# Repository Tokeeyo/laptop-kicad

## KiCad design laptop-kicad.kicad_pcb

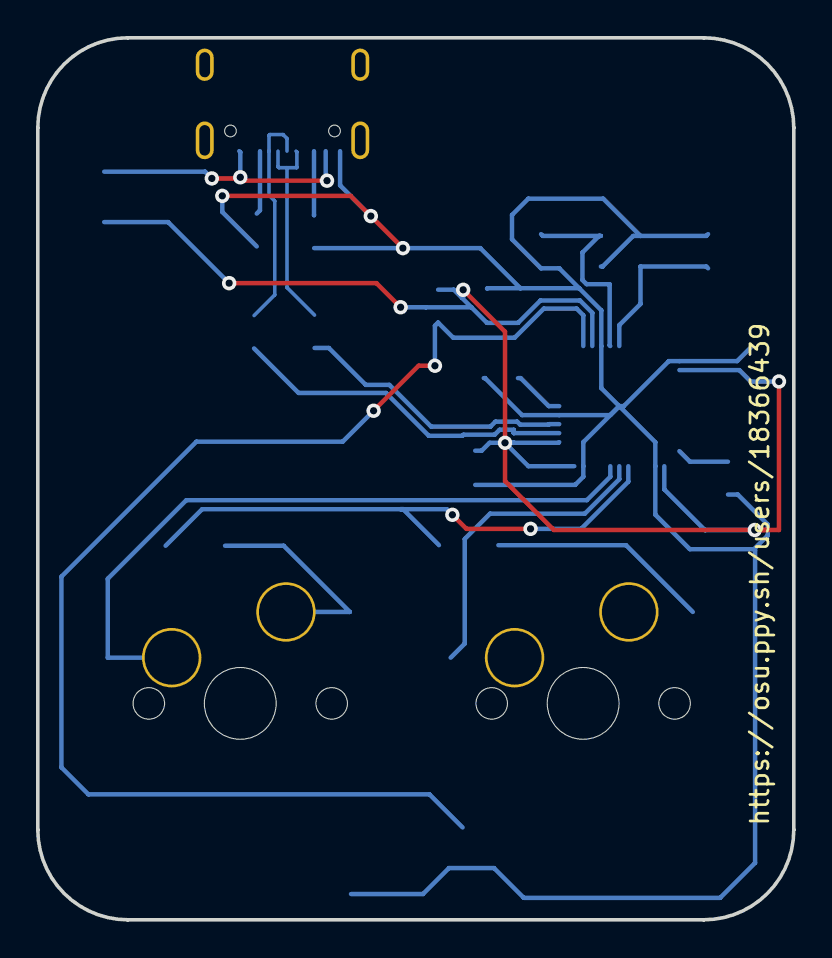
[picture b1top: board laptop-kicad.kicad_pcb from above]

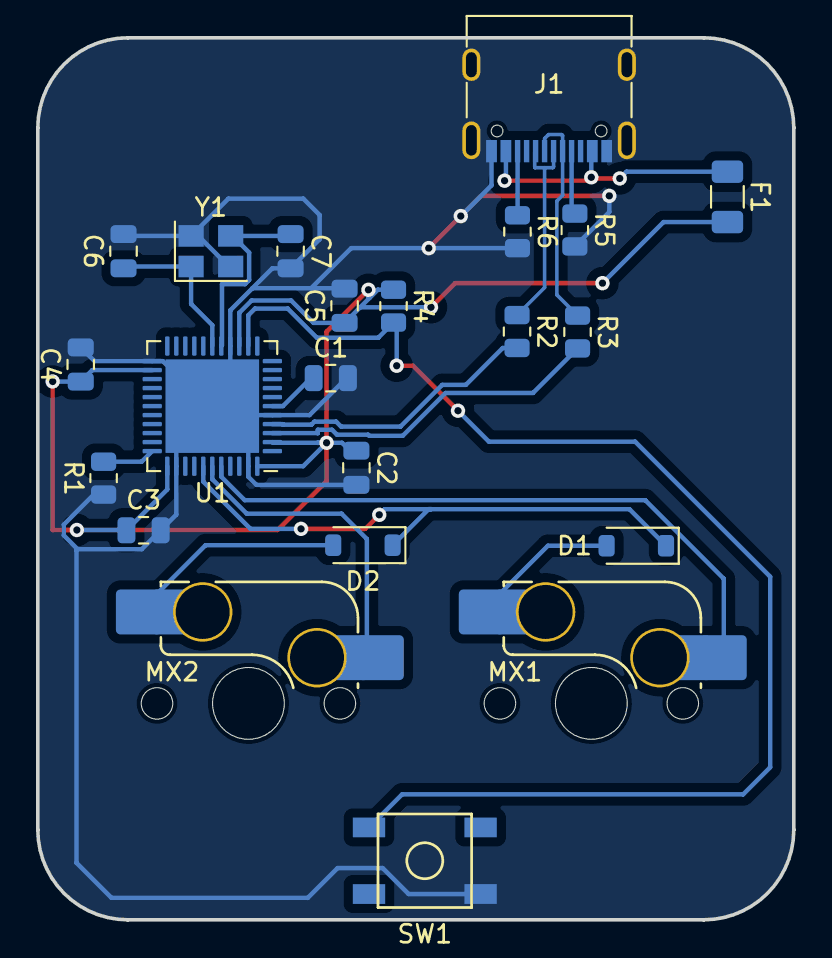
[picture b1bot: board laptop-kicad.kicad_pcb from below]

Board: 2 copper layers, 42.0 x 49.0 mm, 22 parts (22 on the bottom side), 19 nets.

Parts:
C1: 1uF; C_0805_2012Metric
C2, C3, C4: 0.1uF; C_0805_2012Metric
C5: 10uF; C_0805_2012Metric
C6, C7: 22pF; C_0805_2012Metric
D1, D2: D_Small; D_SOD-123
F1: 500mA; Fuse_1206_3216Metric
J1: USB_C_Receptacle_USB2.0; USB_C_Receptacle_G-Switch_GT-USB-7010ASV
MX1, MX2: MX_SW_HS; SW_MX_HS_1u
R1, R4: 10k; R_0805_2012Metric
R2, R3: 22; R_0805_2012Metric
R5, R6: 5.1k; R_0805_2012Metric
SW1: SW_Push; SKQG-1155865
U1: ATmega32U4-M; QFN-44-1EP_7x7mm_P0.5mm_EP5.2x5.2mm
Y1: 16MHz; Crystal_SMD_3225-4Pin_3.2x2.5mm

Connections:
+5V: C2.1, C3.1, C4.1, C5.1, F1.2, R4.1, U1.2 (UVCC), U1.7 (VBUS), U1.14 (VCC), U1.24 (AVCC), U1.34 (VCC), U1.44 (AVCC)
COL0: MX1.1, U1.40 (PF1)
COL1: MX2.1, U1.39 (PF4)
DBUS+: J1.A6 (D+), J1.B6 (D+), R2.1
DBUS-: J1.A7 (D-), J1.B7 (D-), R3.1
GND: C1.2, C2.2, C3.2, C4.2, C5.2, C6.2, C7.1, J1.A1 (GND), J1.A12 (GND), J1.B1 (GND), J1.B12 (GND), J1.S1 (SHIELD), R1.1, R5.2, R6.2, SW1.1, U1.5 (UGND), U1.15 (GND), U1.23 (GND), U1.35 (GND), U1.43 (GND), U1.45 (GND), Y1.2, Y1.4
unnamed: D1.2 (A), MX1.2
unnamed: D2.2 (A), MX2.2
unnamed: J1.A5 (CC1), R5.1
unnamed: J1.B5 (CC2), R6.1
unnamed: R2.2, U1.4 (D+)
unnamed: R3.2, U1.3 (D-)
unnamed: C1.1, U1.6 (UCAP)
unnamed: C6.2, U1.17 (XTAL1), Y1.1
unnamed: C7.2, U1.16 (XTAL2), Y1.3
unnamed: R1.2, U1.33 (~HWB/PE2)
unnamed: R4.2, SW1.2, U1.13 (~RESET)
ROW0: D1.1 (K), D2.1 (K), U1.38 (PF5)
VBUS: F1.1, J1.A4 (VBUS), J1.A9 (VBUS), J1.B4 (VBUS), J1.B9 (VBUS)

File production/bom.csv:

Designator,Footprint,Quantity,Value,LCSC Part #
C1,0805,1,1uF,
"C2, C3, C4",0805,3,0.1uF,
C5,0805,1,10uF,
"C6, C7",0805,2,22pF,
"D1, D2",D_SOD-123,2,D_Small,
F1,1206,1,500mA,
J1,USB_C_Receptacle_G-Switch_GT-USB-7010ASV,1,USB_C_Receptacle_USB2.0,
"MX1, MX2",SW_MX_HS_1u,2,MX_SW_HS,
"R1, R4",0805,2,10k,
"R2, R3",0805,2,22,
"R5, R6",0805,2,5.1k,
SW1,SKQG-1155865,1,SW_Push,
U1,QFN-44-1EP_7x7mm_P0.5mm_EP5.2x5.2mm,1,ATmega32U4-M,
Y1,Crystal_SMD_3225-4Pin_3.2x2.5mm,1,16MHz,

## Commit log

2023-04-12 stuff
2023-04-12 big progress
2023-04-12 its 4am dood
2023-04-14 redoing everything
2023-04-15 PCB is done pt 2
2023-04-15 Zykrah Edits
2023-04-16 changing tide
